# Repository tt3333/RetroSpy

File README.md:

[Click here for instructions for use with Raspberry Pi Pico](docs/README-RaspberryPiPico.md)<br>
[Raspberry Pi Picoでの使用方法はこちら](docs/README-RaspberryPiPico-ja.md)

The following is the Readme of the original RetroSpy<br>
以下は本家RetroSpyのReadme

# RetroSpy

#### [Download the latest RetroSpy release here.](https://github.com/retrospy/RetroSpy/releases/latest)

A fork of [NintendoSpy](https://github.com/jaburns/NintendoSpy), RetroSpy is designed to present controller inputs from a console or computer in a display window.  This allows you to show your controller inputs for things like speedrunning, game tutorials, and more.  You can also convert controller presses into keystrokes to control programs on your computer such as LiveSplit and OBS.  RetroSpy supports the following systems and their regional equivalents:

## Second Generation
* Atari 2600 [joysticks](https://retro-spy.com/wiki/retrospy-hardware-selection/), [driving](https://retro-spy.com/wiki/atari-driving-controller-on-arduino-getting-started/) & [keyboard](https://retro-spy.com/wiki/atari-keyboard-controller-on-arduino-getting-started/) controllers, the [Omega Race booster grip](https://retro-spy.com/wiki/atari-omega-race-booster-grip-on-arduino-getting-started/) and [paddles](https://retro-spy.com/wiki/atari-paddles-on-arduino-getting-started/) 
* [Mattel Intellivision](https://retro-spy.com/wiki/intellivision-on-arduino-getting-started/) 
* Coleco ColecoVision [standard and Super Action controllers](https://retro-spy.com/wiki/coleco-colecovision-controllers-on-arduino-getting-started/) 
* [Atari 5200](https://retro-spy.com/wiki/coleco-colecovision-controllers-on-arduino-getting-started/)

## Third Generation
 - [NES](https://retro-spy.com/wiki/retrospy-hardware-selection/)
 - Atari 7800 [joysticks](https://retro-spy.com/wiki/atari-omega-race-booster-grip-on-arduino-getting-started/) and [paddles](https://retro-spy.com/wiki/atari-paddles-on-arduino-getting-started/)
 - [Sega Master System](https://retro-spy.com/wiki/retrospy-hardware-selection/)
 - [Commodore 64 Games System](https://retro-spy.com/wiki/retrospy-hardware-selection/)

## Fourth Generation
 - NEC PC Engine/TurboGraphx-16/SuperGrafx [2, 3 and 6-button controllers](https://retro-spy.com/wiki/turbografx-16-pc-engine-on-arduino-getting-started/)
 - Sega Genesis [3/6-button controllers and the Mega Mouse](https://retro-spy.com/wiki/retrospy-hardware-selection/)
 - SNK Neo Geo [Arcade Sticks and Neo Geo CD controllers](https://retro-spy.com/wiki/neo-geo-on-arduino-getting-started/)
 - Commodore CDTV [wirelesss remotes](https://retro-spy.com/wiki/cdtv-wireless-remotes-on-arduino-getting-started/), [wired mice/joysticks](https://retro-spy.com/wiki/cdtv-wired-mouse-joystick-on-arduino-getting-started/) and [keyboards](https://retro-spy.com/wiki/cdtv-keyboard-on-arduino-getting-started/)
 - SNES [controllers and mice](https://retro-spy.com/wiki/retrospy-hardware-selection/)
 - Philips CD-i [wireless remotes](https://retro-spy.com/wiki/cdi-wireless-remotes-on-arduino-getting-started/) and [wired controllers](https://retro-spy.com/wiki/cdi-wired-controllers-on-arduino-getting-started/)

## Fifth Generation
 - Fujitsu FM Towns Marty [controllers](https://retro-spy.com/wiki/fm-towns-controllers-on-arduino-getting-started/), [mice](https://retro-spy.com/wiki/fm-towns-marty-mouse-on-teensy-getting-started/) and [keyboards](https://retro-spy.com/wiki/fm-towns-marty-keyboard-on-teensy-getting-started/)
 - Amiga CD32 [controllers](https://retro-spy.com/wiki/amiga-cd32-on-teensy-getting-started/), [analog joysticks](https://retro-spy.com/wiki/amiga-analog-joysticks-on-arduino/), [mice](https://retro-spy.com/wiki/amiga-analog-joysticks-on-arduino/), [classic Atari-style joysticks](https://retro-spy.com/wiki/retrospy-hardware-selection/) and [keyboards](https://retro-spy.com/wiki/cd32-keyboard-on-arduino-getting-started/)
 - 3DO [controllers and mice](https://retro-spy.com/wiki/3do-on-arduino-getting-started/)
 - Atari Jaguar [Standard and Pro controllers](https://retro-spy.com/wiki/jaguar-on-arduino-getting-started/)
 - Sega Saturn [digital controllers, the 3D Control Pad and the Shuttle Mouse](https://retro-spy.com/wiki/retrospy-hardware-selection/)
 - Sony PlayStation [digital controllers, dual analog controllers, DualShock 1/2 controllers and mice](https://retro-spy.com/wiki/playstation-1-2-on-arduino-getting-started/)
 - [NEC PC-FX](https://retro-spy.com/wiki/pc-fx-on-arduino-getting-started/)
 - [Bandai Pippin](https://retro-spy.com/wiki/pippin-on-arduino-getting-started/)
 - [Nintendo VirtualBoy](https://retro-spy.com/wiki/retrospy-hardware-selection/)
 - Nintendo 64 [controllers and mice](https://retro-spy.com/wiki/retrospy-hardware-selection/)

## Sixth Generation
 - Sega Dreamcast [controllers and mice](https://retro-spy.com/wiki/dreamcast-on-teensy-getting-started/) 
 - Sony PlayStation 2 [digital controllers, dual analog controllers, DualShock 1/2 controllers and mice](https://retro-spy.com/wiki/playstation-1-2-on-arduino-getting-started/)
 - Nintendo GameCube [controllers](https://retro-spy.com/wiki/retrospy-hardware-selection/) 
 - Microsoft Xbox [controllers](https://retro-spy.com/wiki/retrospy-usb-based-controller-getting-started/)

## Seventh Generation
 - Microsoft Xbox 360 [wired controllers](https://retro-spy.com/wiki/retrospy-usb-based-controller-getting-started/)
 - [PlayStation 3](https://retro-spy.com/wiki/retrospy-usb-based-controller-getting-started/)
 - Nintendo Wii [extension controllers](https://retro-spy.com/wiki/wii-on-teensy-getting-started/)

## Eigth Generation
 - Nintendo Wii U [extension controllers](https://retro-spy.com/wiki/wii-on-teensy-getting-started/) 
 - [PlayStation 4](https://retro-spy.com/wiki/retrospy-usb-based-controller-getting-started/)
 - Nintendo Switch [wired controllers](https://retro-spy.com/wiki/retrospy-usb-based-controller-getting-started/)

## Classic/Mini Consoles
 - [Nintendo NES Classic](https://retro-spy.com/wiki/wii-on-teensy-getting-started/)
 - [Nintendo SNES Classic](https://retro-spy.com/wiki/wii-on-teensy-getting-started/)
 - [The C64 Mini](https://retro-spy.com/wiki/retrospy-usb-based-controller-getting-started/)
 - [Sony PlayStation Classic](https://retro-spy.com/wiki/retrospy-usb-based-controller-getting-started/)
 - [SNK Neo Geo Mini](https://retro-spy.com/wiki/retrospy-usb-based-controller-getting-started/)
 - [Sega Genesis Mini](https://retro-spy.com/wiki/retrospy-usb-based-controller-getting-started/)
 - [NEC TurboGrafx-16 Mini](https://retro-spy.com/wiki/retrospy-usb-based-controller-getting-started/)

## MiSTer
 - [USB controllers](https://retro-spy.com/wiki/setting-up-retrospy-for-the-mister/)

## To-Do List
 - 8Bitdo Wireless Bluetooth Controller Adapter on Switch
 - Xbox One
 - NEOGEO Arcade Stick Pro
 - Pippin Wireless Controllers

## Wishlist
 - ColecoVision Steering Wheel
 - Atari 5200 Trackball Controller
 - Steel Battalion Xbox Controller
 - CDTV Trackball
 - Genesis XE-1 AP
 - Nuon
 - HyperScan
 - Casio Loopy
 - Bandai Playdia

## Special Thanks 
Big thanks to Brian Khuu and other [contributors](https://github.com/mofosyne/arduino-gameboy-printer-emulator#contributors--thanks) for decoding the GBP protocol and making Arduino Game Boy Printer Emulator, which can be found at  https://github.com/mofosyne/arduino-gameboy-printer-emulator.

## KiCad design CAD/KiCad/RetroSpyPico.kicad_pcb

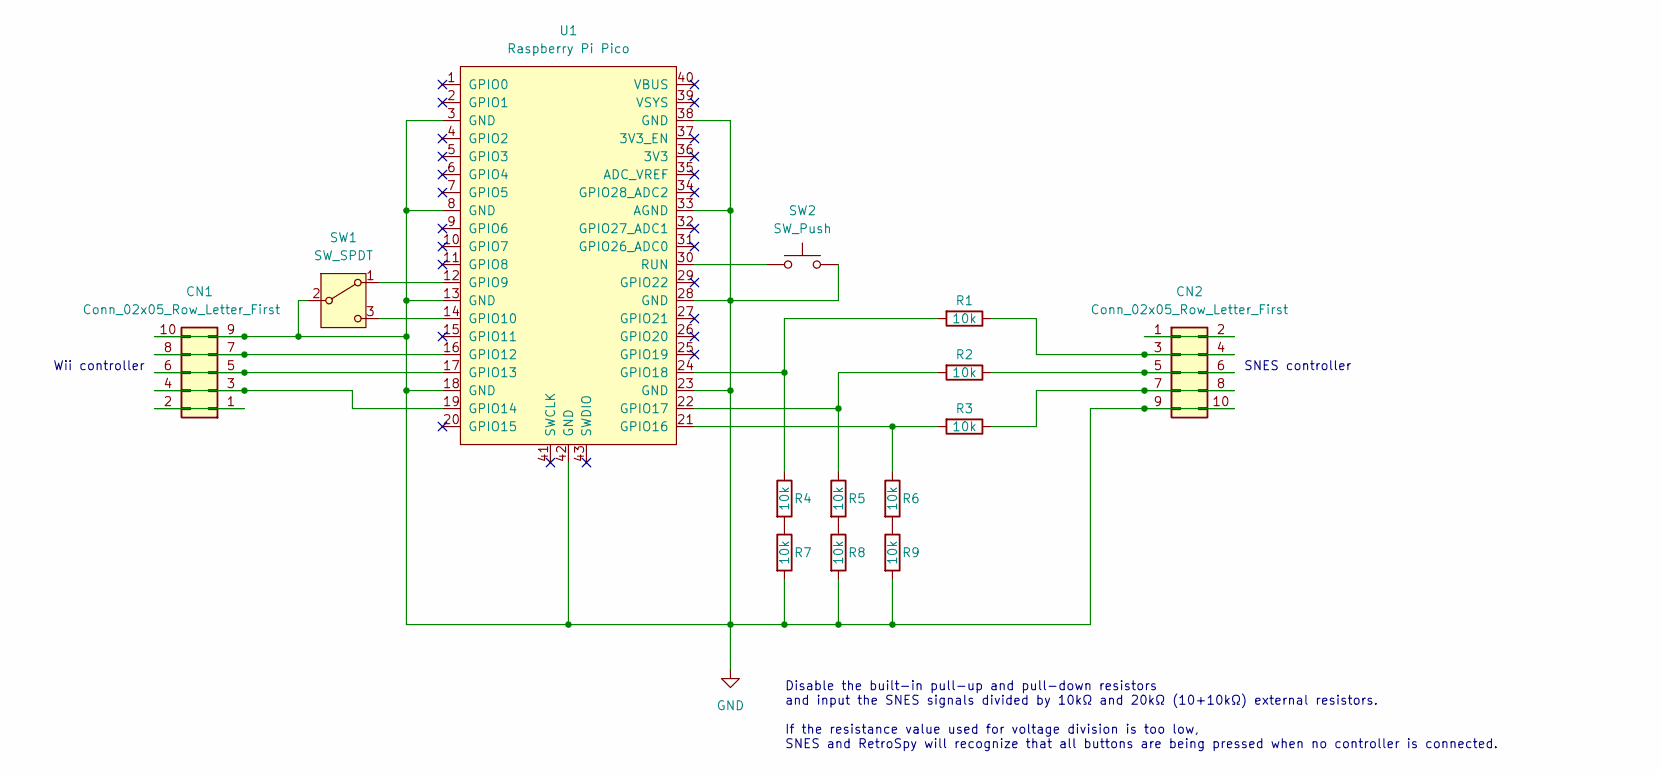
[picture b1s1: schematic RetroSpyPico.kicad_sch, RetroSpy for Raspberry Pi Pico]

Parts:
CN1, CN2: Conn_02x05_Row_Letter_First; PinHeader_2x05_P2.54mm_Vertical
R1, R2, R3, R4, R5, R6, R7, R8, R9: 10k; R_Axial_DIN0207_L6.3mm_D2.5mm_P10.16mm_Horizontal
SW1: SW_SPDT; PinHeader_1x03_P2.54mm_Vertical
SW2: SW_Push; SW_PUSH_6mm
U1: Raspberry Pi Pico; RPi_Pico_SMD_TH

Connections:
GND: CN1.9, CN1.10, CN2.9, CN2.10, R7.2, R8.2, R9.2, SW1.2 (B), SW2.2, U1.3 (GND), U1.8 (GND), U1.13 (GND), U1.18 (GND), U1.23 (GND), U1.28 (GND), U1.33 (AGND), U1.38 (GND), U1.42 (GND)
unnamed: CN1.1, CN1.2
unnamed: CN1.3, CN1.4, U1.19 (GPIO14)
unnamed: CN1.5, CN1.6, U1.17 (GPIO13)
unnamed: CN1.7, CN1.8, U1.16 (GPIO12)
unnamed: CN2.1, CN2.2
unnamed: CN2.3, CN2.4, R1.1
unnamed: CN2.5, CN2.6, R2.1
unnamed: CN2.7, CN2.8, R3.1
unnamed: R4.2, R7.1
unnamed: R5.2, R8.1
unnamed: R6.2, R9.1
unnamed: SW1.1 (A), U1.12 (GPIO9)
unnamed: SW1.3 (C), U1.14 (GPIO10)
unnamed: R3.2, R6.1, U1.21 (GPIO16)
unnamed: R2.2, R5.1, U1.22 (GPIO17)
unnamed: R1.2, R4.1, U1.24 (GPIO18)
unnamed: SW2.1, U1.30 (RUN)

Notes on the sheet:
Wii controller
Disable the built-in pull-up and pull-down resistors and input the SNES signals divided by 10kΩ and 20kΩ (10+10kΩ) external resistors. If the resistance value used for voltage division is too low, SNES and RetroSpy will recognize that all buttons are being pressed when no controller is connected.
SNES controller

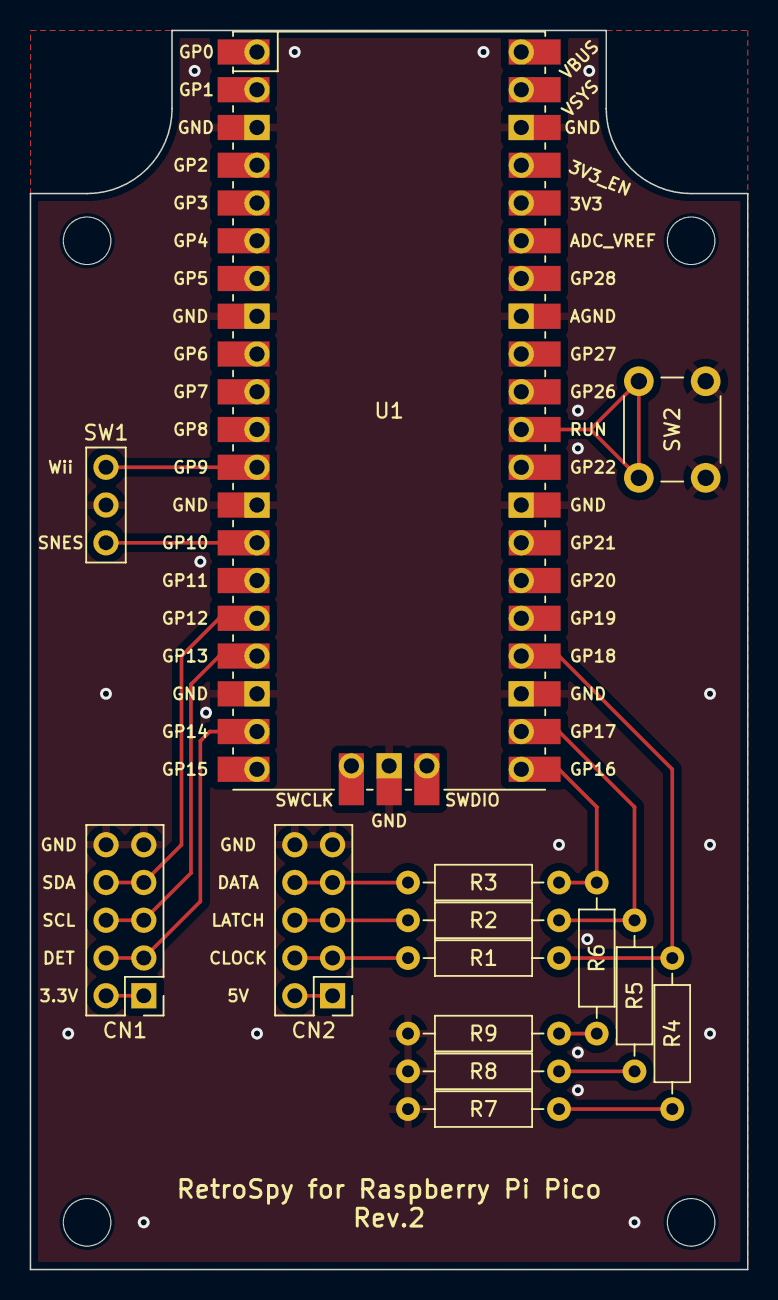
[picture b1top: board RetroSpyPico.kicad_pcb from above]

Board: 2 copper layers, 48.3 x 83.4 mm, 14 parts (0 on the bottom side), 18 nets.

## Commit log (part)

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2021-12-04 Two instances of RetroSpy can now be connected to different controllers on the same MiSTer.
2021-12-09 Luigi's mansion now registers the right analog trigger.
2021-12-09 moved a variable to where it belonged
2021-12-09 Fixed SSHMonitor from hanging when the device was disconnected.
2021-12-09 Fixed random bug in TG16 firmware
2021-12-09 Accidently left mousetester in the skin
2021-12-10 First attempt at fake stick movements on Saturn Twin Stick
2021-12-11 Added x & y precision attributes to sticks to create a deadzone for off center sticks. Also finally fixed teh float parse error in skins
2021-12-11 Initial Nuon. All digital buttons work. Analog is still a mystery
2021-12-18 Nuon Analog Controller Support
2021-12-18 Line endings
2021-12-19 First attempt at VCS reader
2021-12-19 Added VCS support
2021-12-19 Missed a file
2021-12-21 Added PrintSize option in to GBP Emulator
2021-12-22 Updating gameboy printer firmware to 3.1
2021-12-24 Updating version number and fixing build time in About window
2022-01-12 Support for VTech V.Smile console.
2022-01-12 Adding V.Flash firmware
2022-01-14 Adding config files to .zip and installer
2022-01-14 Fixed GBP emulator to know when the image is done printing.
2022-01-14 incremented installer version to 5.0.2
2022-01-31 Specifically look for the SN30 instead of assuming SN30 when no direction is pressed.
2022-02-06 Added startup message to Wii
2022-03-06 Fixed build break
2022-04-21 Removed SSH settings in MiSTer
2022-04-21 Update to 2022
2022-04-24 Removing BuildData.txt from git
2022-04-24 Clean up some settings
2022-04-27 Maybe work
2022-04-27 Updating project to build Nano Every firmware
2022-04-30 Theoretically this support the Nano Every, but I have only physically tested NES.
2022-05-03 Added support for LGT8F328 boards.
2022-05-11 Added PS4 via Cronus Zen
2022-05-12 Forgot this change.
2022-05-15 SerialMonitor.cs: Added Request To Send Handshake & Data Terminal Ready = True. Improves connection/reconnection with certain devices. atgema32u4 (arduino pro micro) Gamecube.cs: Added support for Ni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
2022-06-03 A500 Mini Support
2022-06-25 Nintendo64.cs: added support for nicohood byte packet format
2022-11-02 support multi core (Raspberry Pi Pico only)
2022-11-02 add .gitkeep
2022-11-02 add README-RaspberryPiPico.md
2022-11-02 add binary
2022-11-23 Weird file got added, removing it.
2022-11-23 Upping version number.
2022-11-24 Change SerialMonitor timer priority to 'Normal', reflecting gamepad state in the ui much faster than default (background) priority
2022-11-24 Allowing crazy workaround for Switch Pro Controller on PC.
2022-11-25 This theoretically works.
2022-11-25 add SNES support for RaspberryPiPico
2022-11-25 Added an actual nop
2022-11-25 N64, Gamecube and Dreamcast are all available on the Teensy 4.x
2022-11-25 Upping time before we detect a disconnect from the MiSTer by 10x.
2022-11-29 For project file
2022-12-01 Forgot palettes config file.
2022-12-02 Compression now works on GBPemu.
2022-12-02 Cleaned up GBPemu code a bit
2022-12-05 Genesis Mini 2 has to be seperate since Genesis Mini 1 apparently requires high speed USB and the Mini 2 requires full speed USB.
2022-12-05 Forgot to add it to the USB list
2022-12-05 Re-paletting is now based on the original tiles and not the colored pixel buffer.
2022-12-05 Fixed a crashing bug that I introduced with custom palettes.
2022-12-06 Added a failsafe check in case Selected Palette manages to get set to -1.
2022-12-08 Fix a build break for Teensy 4.1
2022-12-08 Fixed a build break for Teensy 4.1
2022-12-08 Added some better error handling in Dreamcast reader
2022-12-08 Updating Code Anaylzers to 7.0
2022-12-08 Restructured firmware.ino and added startup messages to all firmwares.
2022-12-08 Checking in VersionGen
2022-12-09 Added kernel update to USB updater
2022-12-09 Moving the copy of kernel up.
2022-12-16 Fixed a crashing bug if you change the palette before printing an image.
2022-12-24 Can now toggle the COM port autodetection in GBEmu.
2022-12-28 Fully functioning Setup, About and Add/Remove dialogs.
2022-12-28 Added skins and made SharpDX into a nuget reference.
2022-12-28 Added command line parameters processsing.
2022-12-29 Cleaning up code
2022-12-29 More cleanup
2022-12-29 Cleanup
2022-12-29 Clean up
2022-12-29 cleaning up
2022-12-30 release sort of works.
2022-12-30 Fixed Analog triggers
2022-12-30 ViewWindow resize now works.
2023-01-01 SendKey replaced with Desktop.Robot. With the exception of analog range modification SharpDX is replaced with Vortice.DirectInput. Win32 XInput replaced with Vortice.XInput
2023-01-01 More cross platform shenanigans.
2023-01-01 more cross platform shenanigans
2023-01-01 One of these days it will start in Linux
2023-01-01 More cross platform crap
2023-01-01 More case sensitivity
2023-01-02 Trying to find serial ports in Linux
2023-01-02 Serial ports
2023-01-02 Forgot to implement Save in the GBP Viewer
2023-01-02 Adding Carlito font for better cross platform looks.
2023-01-02 Some changes
2023-01-02 Attempting to get GBPemu working
2023-01-02 Attempting to tweak the GBPemu autodetect for Linux
2023-01-02 Fixing serial monitor for newer done with printing detection
2023-01-02 Some more tweaks in GBPemu for Linux
2023-01-02 Hacked up autodetect for linux
2023-01-02 Unded hacky linux autodetect and just made it so you can undo disable autodetect for now
2023-01-02 Fiddling with COM Menu in Linux
2023-01-02 Fixed GBPUpdater to work in Linux
2023-01-03 Removing a duplicate using
2023-01-03 Adding sed to fix a problem in nightly release
2023-01-03 Adding linux release script
2023-01-03 Adding macos and Linux builds to release script.
2023-01-04 fixing release.sh
2023-01-04 testing
2023-01-04 revert testing.
2023-01-04 I have no patrons!
2023-01-04 Switched a bunch of if Linux to if !Windows to hopefully smooth over the porting to mac
2023-01-04 Added solution for machines without VisualGDB
2023-01-04 Fixing build date
2023-01-04 Changing about to be an external webpage
2023-01-04 Ignoring BuildDate.txt
2023-01-04 Adding avrdude support for macOS
2023-01-04 fixing
2023-01-04 Adding mac release script
2023-01-04 changing permissions on mac release script
2023-01-04 Fixing autodetection in GBPUpdater
2023-01-05 Attempt at Linux joystick
2023-01-05 Cleaniup
2023-01-05 Attempt at Linux Keyboard & Mouse
2023-01-05 Trying again
2023-01-05 Updating linux keyboard and mouse
2023-01-06 Fixing signing
2023-01-06 adding explict runtime flag
2023-01-06 Mac binaries are now signed and noterized
2023-01-06 Removing the rest of secrets
2023-01-06 more secrets
2023-01-06 Mac builds should be good now
2023-01-07 Fixed Link's Awakening DX in the GBPemu.
2023-01-08 Replacing Assembly.Location with AppContext.BaseDirectory
2023-01-08 git pull in release script is wrong
2023-01-08 Fat binaries should be workign now
2023-01-08 oops
2023-01-08 still tweaking mac release script
2023-01-08 Working on mac apps
    Working on generating apps
2023-01-08 Still teaking
2023-01-08 tweaking mac script
2023-01-09 trying for the 100th time
2023-01-09 again
2023-01-09 reverting
2023-01-09 Mac release script works
2023-01-09 More paths messed up
2023-01-09 getting unified macos build
2023-01-09 Mac distro works
2023-01-09 missed a file
2023-01-09 Adding code so the app bundles can find their user changable files.
2023-01-09 Adding keychain unlock to the mac release script
2023-01-10 Threw together an actual GUI for both updaters.
2023-01-10 Some clean uo
2023-01-10 Cleaned up a bunch of error message handeling
2023-01-10 Prevent keybinding dialog box from going behind view window.
2023-01-10 Adding new GBP firmware files to zip generation
2023-01-10 Putting the setup package back in the release script
2023-01-10 adding single file build
2023-01-10 updating linux release script.
2023-01-11 Tweaking .NET prereq handling
2023-01-11 attempting to get release-mac.sh to run under cron
2023-01-12 Stupid hack for the config file on macs
2023-01-12 Adding creation of fancy dmg
2023-01-13 Workaround to generate dmg in SSH & launchd
2023-01-13 More tweaks
2023-01-13 fixed a minor typo
2023-01-13 Some warning cleanup
2023-01-13 Adding MiSTer install to Mac and Linux releases
2023-01-13 adding logo
2023-01-13 moved logo up
2023-01-14 Have to "comment" out version and firmware state because of GBP emulator crashing
2023-01-14 Checking a fix for Big Sur and Catalina
2023-01-15 Setting icons to windows programs.
2023-01-15 64 bit installer.
2023-01-15 forgot the path
2023-01-16 fileicon command was wrong
2023-01-17 Squeezing out some more memory.
2023-01-17 Adding arm64 build
2023-01-17 build arm64 on linux
2023-01-17 made executable
2023-01-17 minor issue
2023-01-17 tweaking gbpupdater
2023-01-18 Adding USB logo to USBUpdater icons
2023-01-20 Fixed the analog on gamepad reader
2023-01-20 Forgot to add firmware to linux release
2023-01-21 Bumping Version 6.0.1
2023-01-21 Updating SSH assembly
2023-01-21 Mister controller drop down wasn't bound correctly.
2023-01-21 change path to msbuild in release script
2023-01-22 Updating hostname of Vision USB to retrospy.local
2023-01-22 Adding retrospy shortcut to dekstop
2023-01-27 Making the updater abort if it sees stretch installed.
2023-01-28 changing xbox 360 linux command
2023-01-28 forgot to save
2023-01-29 Should really add the license to the install.
2023-01-30 Added support for the Mayflash GameCube Controller Adapter over libusb
2023-01-30 Forgot to add it to linux
2023-01-31 Mor e changes to mmap reader
2023-01-31 adding note about su/sudo on Linux keyboard & mouse
2023-01-31 Moved the hostname resolution of UsbUpdater to .NET
2023-01-31 Missed the files.
2023-02-01 Catch all Exceptions
2023-02-01 Changing how the exe path is determined.
2023-02-02 Bumping version to 6.1
2023-02-03 GBPUpdater and UsbUpdater can now access nightly with a provided GITHUB personal access token
2023-02-04 Fixed the COM ports not being restored from config correctly
2023-02-05 First revision of Vision firmware.
2023-02-05 Expanding the auto build of the Vision firmware.
2023-02-05 Added back some firmwares to Vision firmware and will leave them undocumented.
2023-02-14 Reducing N64 buffer size
2023-02-14 Hopefully all the GND 8 DB-9 controllers work with a Genesis Vision cable.
2023-02-14 Dns.GetHostEntry pukes on raw IP addresses
2023-02-14 Fixing encoding on update-retrospy-installer.sh
2023-02-14 Bumped version to 6.1.1
2023-02-15 Amiga Mouse changes for Vision
2023-02-15 Fixing SMS Sports Pad
2023-02-15 Moved Vision configuration from .ino to common.h
2023-02-19 Changed OutputType to CableType
2023-02-21 Found a type in Generic Gamepad reader
2023-02-21 Bumping version to 6.1.2
2023-02-22 Wii should now work on pins 0 & 1 of Teensy 4 and 4.1
2023-02-22 Made some Vision Ultra tweaks.
2023-02-25 Adding generic USB N64 controller skin to Generic Gamepad
2023-02-25 Added code for Vision CDi
2023-03-03 Bumping to 6.1.3
2023-03-05 add setup1() and loop1()
2023-03-05 reduced differences from the original
2023-03-05 MODE_DETECT support for Raspberry Pi Pico
2023-03-09 disable the built-in pull-down resistors
2023-03-09 add JLCJLCJLCJLC
2023-03-09 supports mode switching during operation (Raspberry Pi Pico only)
2023-03-09 add gerber file
2023-03-09 add schematic.pdf
2023-03-09 Added build setup for Vision ColecoVision
2023-03-11 Fixed a missing StartupMsg message.
2023-03-12 The length of a PS4 packet changed by 1 byte which broke the PS4 Reader.
2023-03-12 Bumping Version to 6.1.4
2023-03-18 Added PS2 controller to linuxjoystick via OSTENT adapter.
2023-03-24 Modifcations required to get building in my build environment,
2023-03-24 Fixing Super Gameboy support
2024-02-21 Corrected a typo in the README
2024-08-09 update KiCad
2024-08-09 add 3D footprint of the Raspberry Pi Pico
    https://github.com/ncarandini/KiCad-RP-Pico/blob/main/RP-Pico%20Libraries/Pico.wrl
2024-08-09 update gerber file
2024-08-09 update schematic
2024-09-13 rename PCB directory
2025-05-02 add FreeCAD project
2025-05-06 update image
2025-05-06 Change CPU speed and optimization to match original RetroSpy.
2025-05-07 If the mode is switched while waiting for an edge, it will now exit the loop.
